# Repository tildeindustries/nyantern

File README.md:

# nyantern
ESP8266 LED lantern

Document: https://docs.google.com/document/d/1sa_9mN3tnlyx4_is4a5Bc_V7Ck8kD285sbXcqGJakbA/

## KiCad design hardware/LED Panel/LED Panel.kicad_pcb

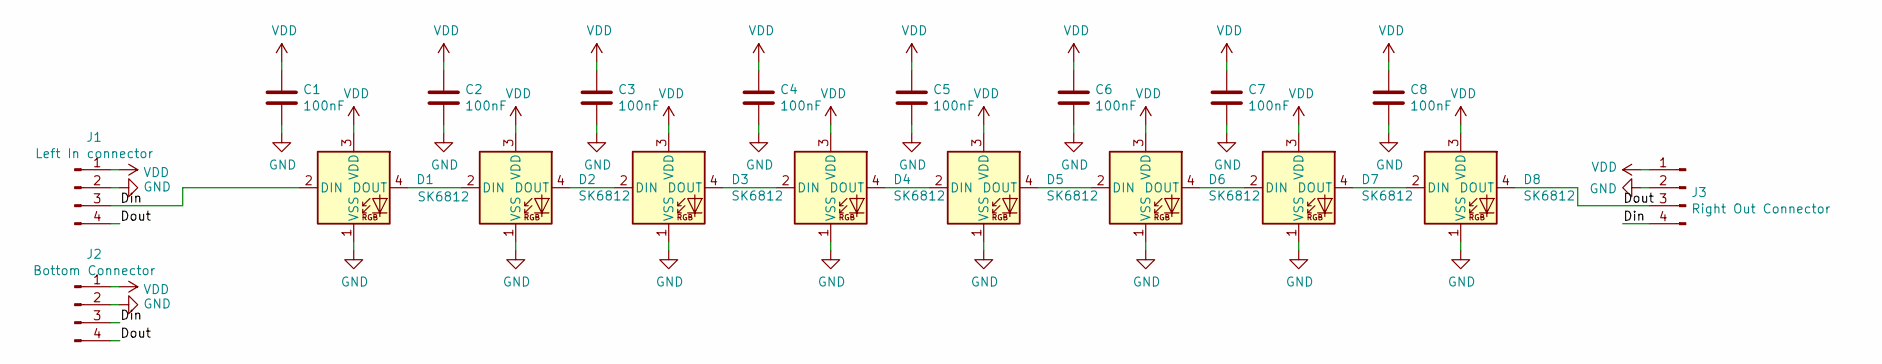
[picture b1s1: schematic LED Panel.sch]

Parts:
C1, C2, C3, C4, C5, C6, C7, C8: 100nF; C_0805_2012Metric
D1, D2, D3, D4, D5, D6, D7, D8: SK6812; LED_SK6812_PLCC4_5.0x5.0mm_P3.2mm
J1: Left In connector; PinSocket_1x04_P2.54mm_Vertical
J2: Bottom Connector; PinSocket_1x04_P2.54mm_Vertical
J3: Right Out Connector; PinSocket_1x04_P2.54mm_Vertical

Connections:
/Din: D1.2 (DIN), J1.3, J2.3, J3.4
/Dout: D8.4 (DOUT), J1.4, J2.4, J3.3
GND: C1.2, C2.2, C3.2, C4.2, C5.2, C6.2, C7.2, C8.2, D1.1 (VSS), D2.1 (VSS), D3.1 (VSS), D4.1 (VSS), D5.1 (VSS), D6.1 (VSS), D7.1 (VSS), D8.1 (VSS), J1.2, J2.2, J3.2
unnamed: D1.4 (DOUT), D2.2 (DIN)
unnamed: D2.4 (DOUT), D3.2 (DIN)
unnamed: D3.4 (DOUT), D4.2 (DIN)
unnamed: D4.4 (DOUT), D5.2 (DIN)
unnamed: D5.4 (DOUT), D6.2 (DIN)
unnamed: D6.4 (DOUT), D7.2 (DIN)
unnamed: D7.4 (DOUT), D8.2 (DIN)
VDD: C1.1, C2.1, C3.1, C4.1, C5.1, C6.1, C7.1, C8.1, D1.3 (VDD), D2.3 (VDD), D3.3 (VDD), D4.3 (VDD), D5.3 (VDD), D6.3 (VDD), D7.3 (VDD), D8.3 (VDD), J1.1, J2.1, J3.1

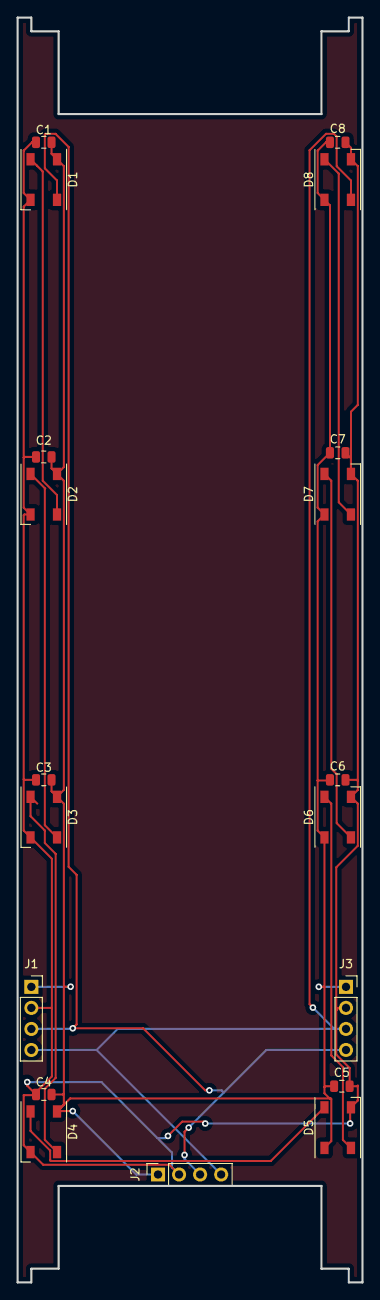
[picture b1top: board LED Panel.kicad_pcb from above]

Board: 2 copper layers, 41.7 x 152.8 mm, 19 parts (0 on the bottom side), 11 nets.

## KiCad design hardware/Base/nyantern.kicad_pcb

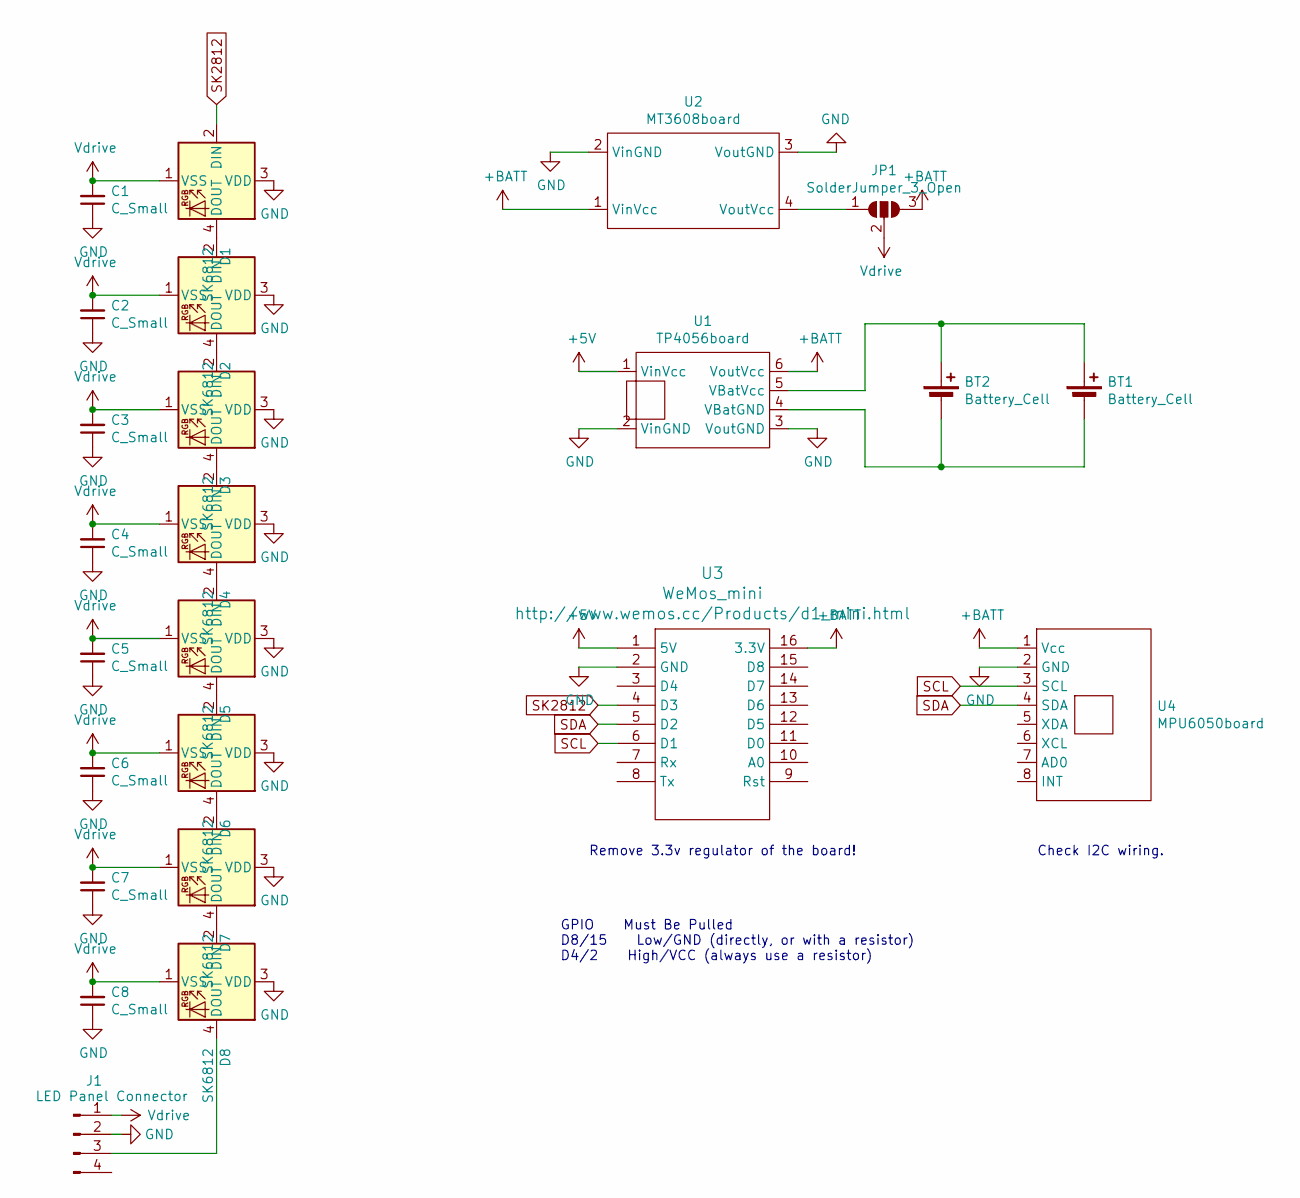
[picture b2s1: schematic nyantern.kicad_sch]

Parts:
BT1, BT2: Battery_Cell; 18650_Holder
C1, C2, C3, C4, C5, C6, C7, C8: C_Small; C_0805_2012Metric
D1, D2, D3, D4, D5, D6, D7, D8: SK6812; LED_SK6812_PLCC4_5.0x5.0mm_P3.2mm
J1: LED Panel Connector; PinSocket_1x04_P2.54mm_Vertical
JP1: SolderJumper_3_Open; SolderJumper-3_P1.3mm_Open_RoundedPad1.0x1.5mm_NumberLabels
U1: TP4056board
U2: MT3608board
U3: WeMos_mini; D1_mini_board
U4: MPU6050board; PinHeader_1x08_P2.54mm_Vertical

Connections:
+5V: U1.1 (VinVcc), U3.1 (5V)
+BATT: JP1.3 (B), U1.6 (VoutVcc), U2.1 (VinVcc), U3.16 (3.3V), U4.1 (Vcc)
GND: C1.1, C2.1, C3.1, C4.1, C5.1, C6.1, C7.1, C8.1, D1.3 (VDD), D2.3 (VDD), D3.3 (VDD), D4.3 (VDD), D5.3 (VDD), D6.3 (VDD), D7.3 (VDD), D8.3 (VDD), J1.2, U1.2 (VinGND), U1.3 (VoutGND), U2.2 (VinGND), U2.3 (VoutGND), U3.2 (GND), U4.2 (GND); also elsewhere on the board
unnamed: BT1.1 (+), BT2.1 (+), U1.5 (VBatVcc)
unnamed: BT1.2 (-), BT2.2 (-), U1.4 (VBatGND)
unnamed: D1.4 (DOUT), D2.2 (DIN)
unnamed 6: D2.4 (DOUT), D3.2 (DIN); also elsewhere on the board
unnamed 7: D3.4 (DOUT), D4.2 (DIN); also elsewhere on the board
unnamed 8: D4.4 (DOUT), D5.2 (DIN); also elsewhere on the board
unnamed: D5.4 (DOUT), D6.2 (DIN)
unnamed 10: D6.4 (DOUT), D7.2 (DIN); also elsewhere on the board
unnamed 11: D7.4 (DOUT), D8.2 (DIN); also elsewhere on the board
unnamed 12: D8.4 (DOUT), J1.3; also elsewhere on the board
unnamed: JP1.1 (A), U2.4 (VoutVcc)
SCL: U3.6 (D1), U4.3 (SCL)
SDA: U3.5 (D2), U4.4 (SDA)
SK2812: D1.2 (DIN), U3.4 (D3)
Vdrive: C1.2, C2.2, C3.2, C4.2, C5.2, C6.2, C7.2, C8.2, D1.1 (VSS), D2.1 (VSS), D3.1 (VSS), D4.1 (VSS), D5.1 (VSS), D6.1 (VSS), D7.1 (VSS), D8.1 (VSS), J1.1, JP1.2 (C); also elsewhere on the board

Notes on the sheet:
GPIO Must Be Pulled D8/15 Low/GND (directly, or with a resistor) D4/2 High/VCC (always use a resistor)
Check I2C wiring.
Remove 3.3v regulator of the board!

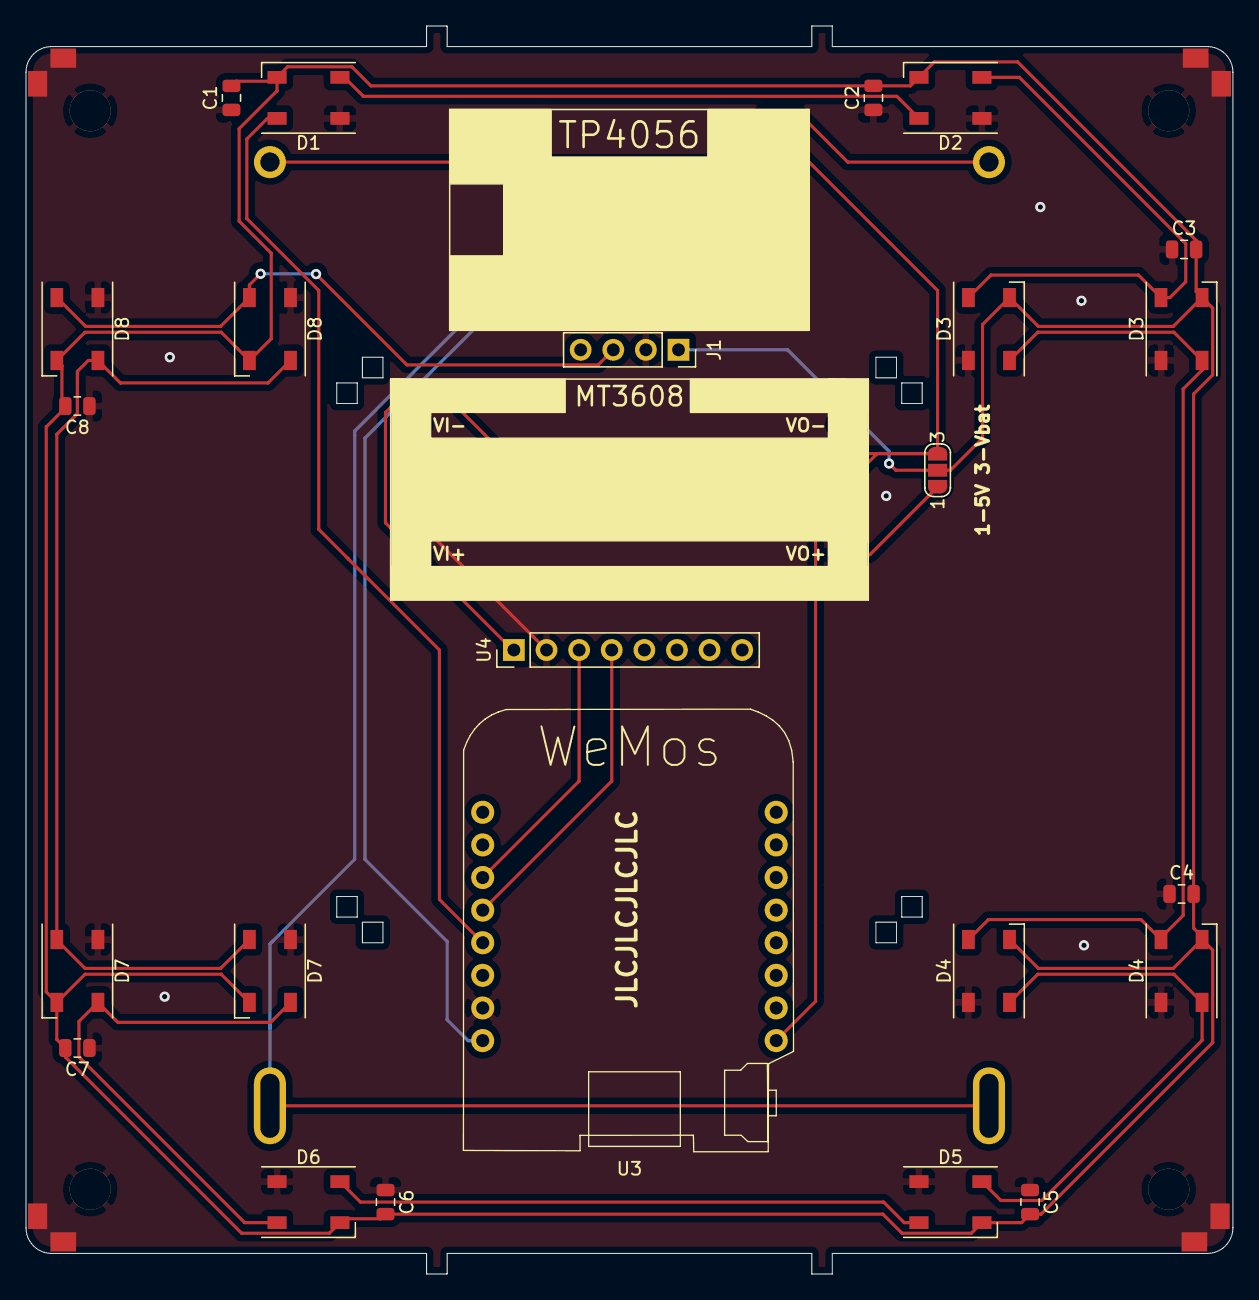
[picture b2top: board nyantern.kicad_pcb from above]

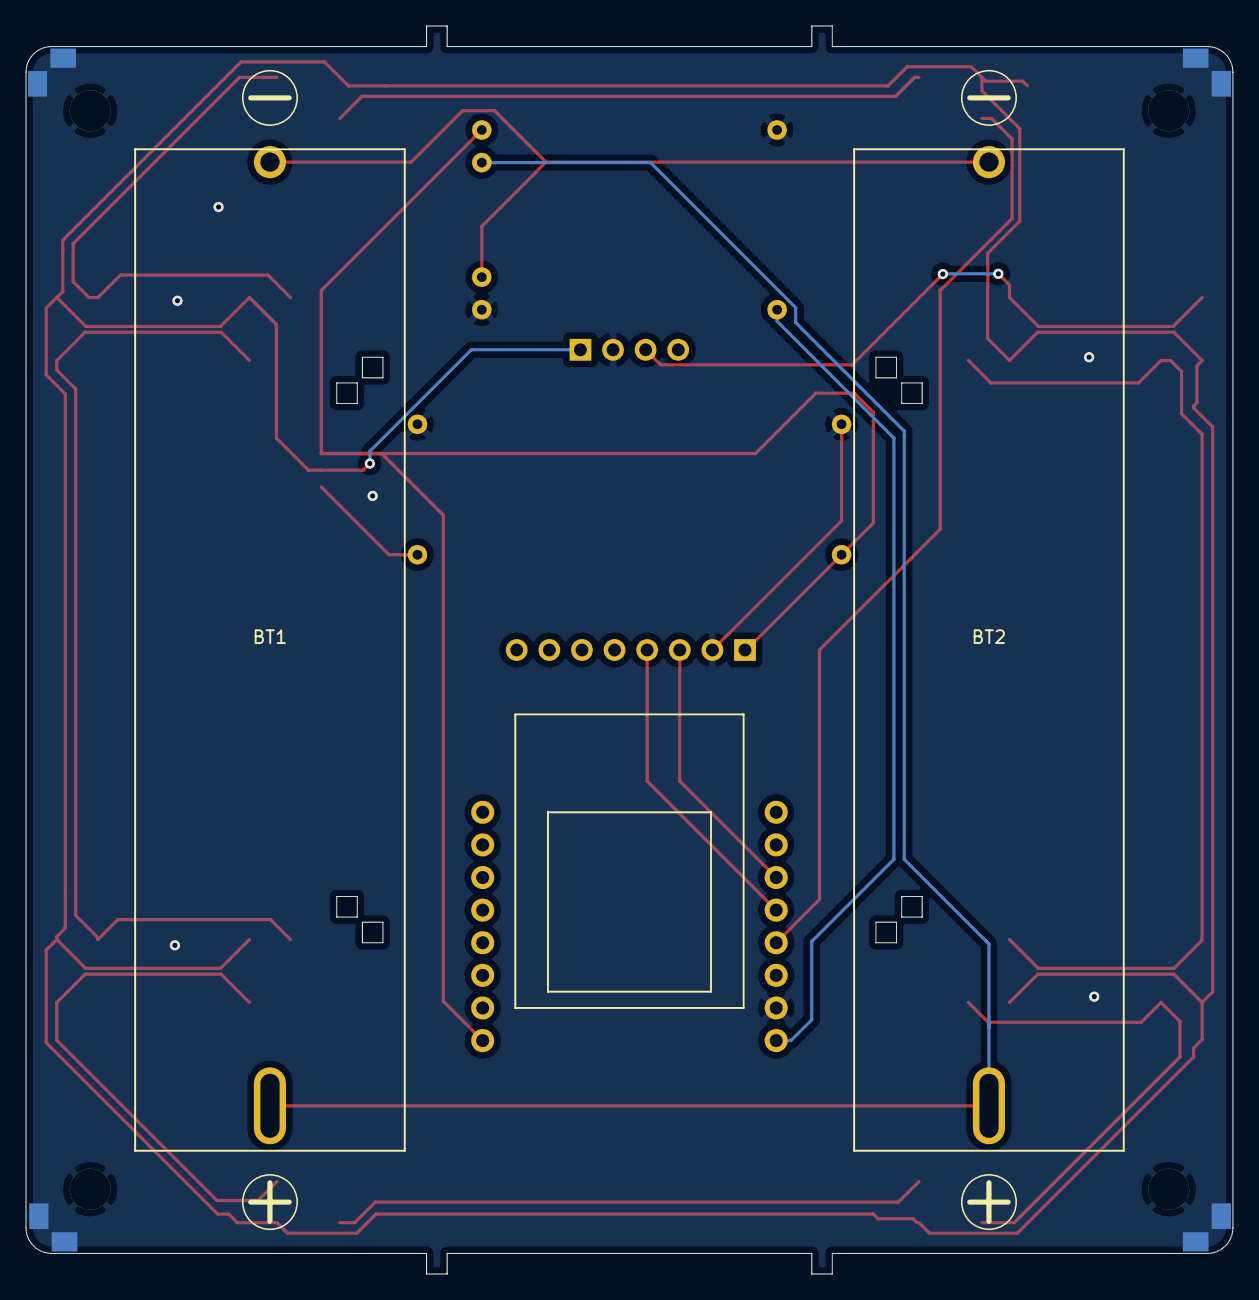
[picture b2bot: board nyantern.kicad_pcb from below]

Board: 2 copper layers, 94.0 x 97.2 mm, 28 parts (2 on the bottom side), 18 nets.

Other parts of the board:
D3#2, D4#2, D7#2, D8#2: SK6812; LED_SK6812_PLCC4_5.0x5.0mm_P3.2mm

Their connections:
GND: D3#2.3, D4#2.3, D7#2.3, D8#2.3; also elsewhere on the board
unnamed 6: D3#2.2; also elsewhere on the board
unnamed 7: D3#2.4, D4#2.2; also elsewhere on the board
unnamed 8: D4#2.4; also elsewhere on the board
unnamed 10: D7#2.2; also elsewhere on the board
unnamed 11: D7#2.4, D8#2.2; also elsewhere on the board
unnamed 12: D8#2.4; also elsewhere on the board
Vdrive: D3#2.1, D4#2.1, D7#2.1, D8#2.1; also elsewhere on the board

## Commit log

2020-08-26 added image
2020-08-26 edited readme
2020-08-31 Prototype schematic made of modules, imported DXF base
2020-09-04 Prototype of mechanical design
2020-09-06 Made footprints for modules and put everything on the board
2020-09-07 First version of the board laid, added monting holes and duplicaded some leds to test out more centered light source
2020-09-21 Progress on mechanical concept, Dinoskin near ready for v1
2020-09-21 resized the board and removed box.py slots, swapped location of battery charging/boost, rounded corners, all yours Gboi
2020-09-23 Mechanical integration of PCB, added pegs and holes on PCB
2020-10-02 Exported 2 sides of the lantern in Kicad, they are missing the solder pad and need a last look at dimensions but should be good Reorganised files in "Hardware" folder
2020-10-10 Added reflective copper on inside Added version with cutout dinoskin Generated gerbers
2021-03-13 God knows but a lot has changed
2025-07-06 dump before reformat
